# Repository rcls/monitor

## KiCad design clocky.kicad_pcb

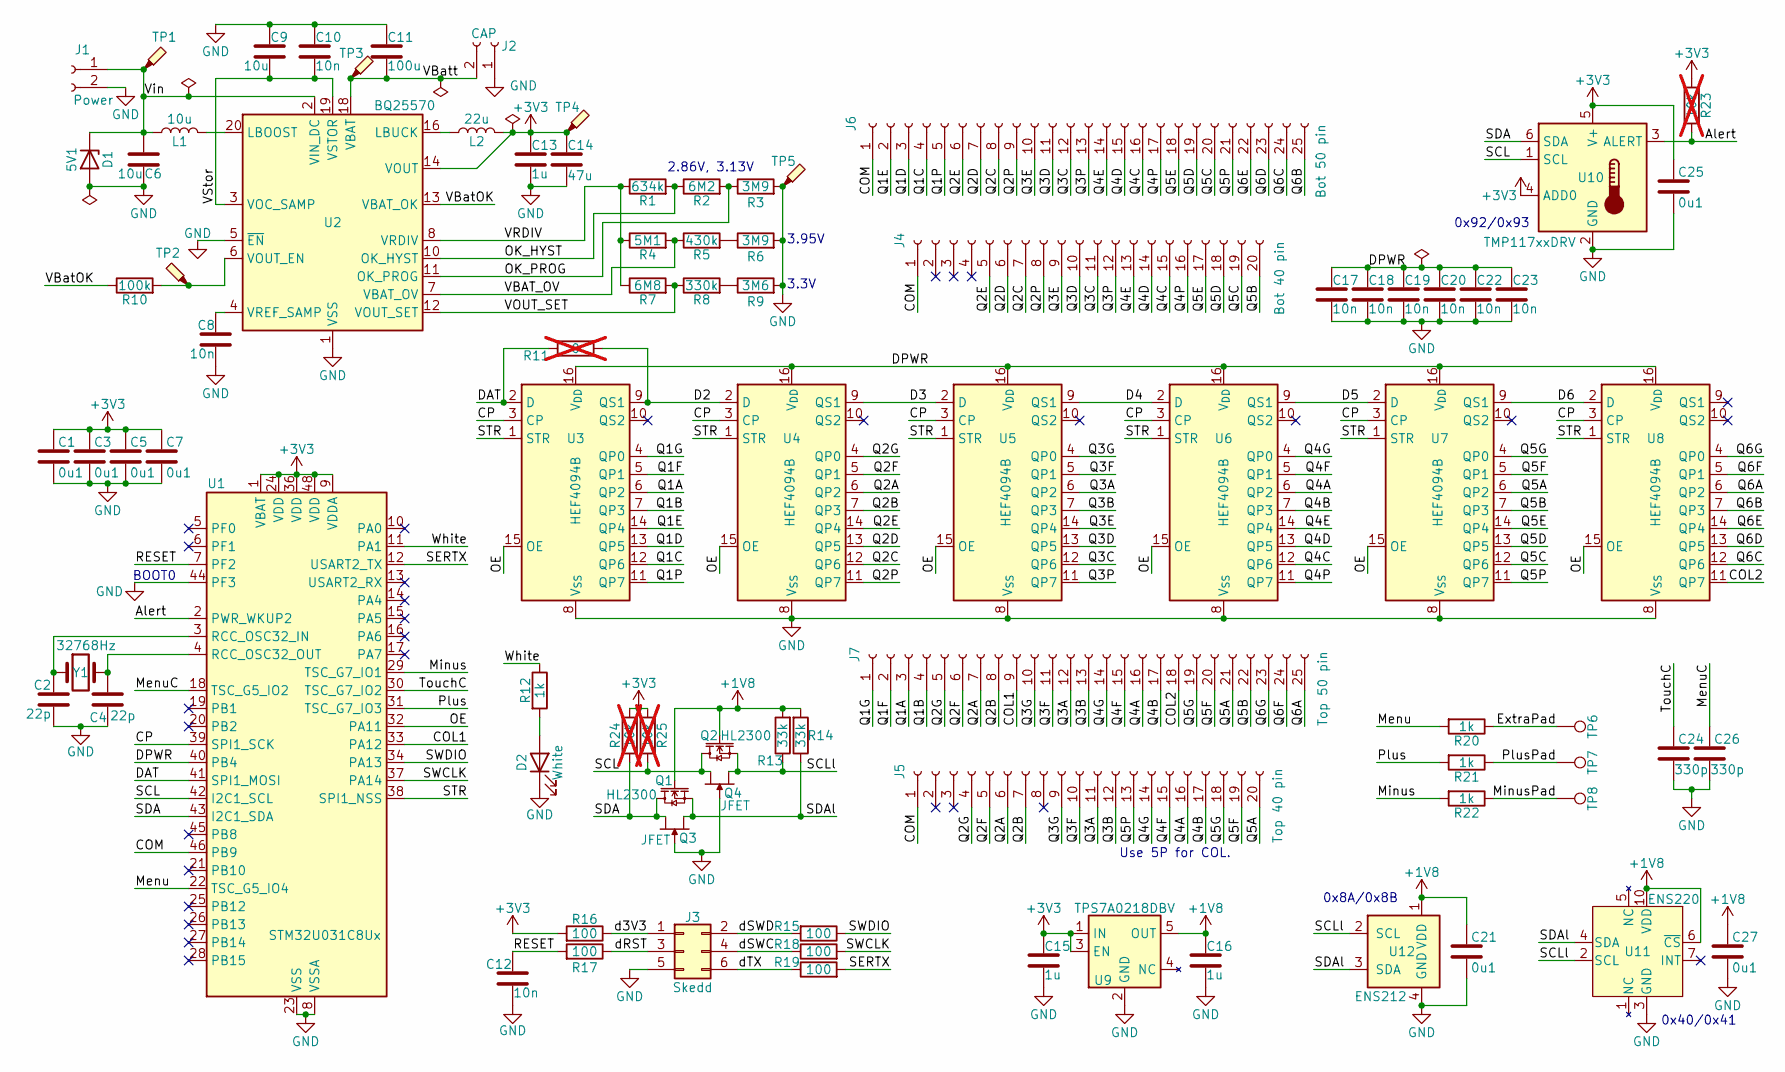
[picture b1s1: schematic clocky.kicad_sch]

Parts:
C1, C3, C5, C7, C21, C25, C27: 0u1; C_0402_1005Metric; JLCPCB C307331
C2, C4: 22p; C_0402_1005Metric; JLCPCB C1555
C6, C9: 10u; C_0603_1608Metric; JLCPCB C19702
C8, C10, C12, C17, C18, C19, C20, C22, C23: 10n; C_0402_1005Metric; JLCPCB C15195
C11: 100u; C_1206_3216Metric; JLCPCB C15008
C13, C15, C16: 1u; C_0402_1005Metric; JLCPCB C52923
C14: 47u; C_0805_2012Metric; JLCPCB C16780
C24, C26: 330p; C_0402_1005Metric; JLCPCB C13533
D1: 5V1; D_SOD-323; JLCPCB C19077434
D2: White; LED_0603_1608Metric; JLCPCB C2290
J1: Power; PinSocket_1x02_P2.54mm_Vertical
J2: CAP; TwoPin_P3.5mm
J3: Skedd; Skedd6
J4: Bot 40 pin; PinSocket_1x20_P2.54mm_Vertical
J5: Top 40 pin; PinSocket_1x20_P2.54mm_Vertical
J6: Bot 50 pin; PinHeader_1x25_P2.54mm_Vertical
J7: Top 50 pin; PinHeader_1x25_P2.54mm_Vertical
L1: 10u; L_0805_2012Metric_Pad1.05x1.20mm_HandSolder
L2: 22u; L_0805_2012Metric_Pad1.05x1.20mm_HandSolder
Q1, Q2: HL2300; SOT-23; JLCPCB C7420343
Q3, Q4: JFET; SOT-23-3
R1: 634k; R_0603_1608Metric
R2: 6M2; R_0603_1608Metric
R3, R6: 3M9; R_0603_1608Metric
R4: 5M1; R_0603_1608Metric
R5: 430k; R_0603_1608Metric; JLCPCB C25969
R7: 6M8; R_0603_1608Metric
R8: 330k; R_0603_1608Metric; JLCPCB C23137
R9: 3M6; R_0603_1608Metric
R10: 100k; R_0402_1005Metric; JLCPCB C25741
R11: 0; R_0603_1608Metric; not fitted
R12, R20, R21, R22: 1k; R_0402_1005Metric; JLCPCB C11702
R13, R14: 33k; R_0603_1608Metric; JLCPCB C4216
R15, R16, R17, R18, R19: 100; R_0402_1005Metric; JLCPCB C25076
R23, R24, R25: 10k; R_0603_1608Metric; not fitted
TP1, TP2, TP3, TP4, TP5: TestPoint_Probe; TestPoint
TP6, TP7, TP8: TestPoint; Dummy
U1: STM32U031C8Ux; QFN-48-1EP_7x7mm_P0.5mm_EP5.6x5.6mm
U2: BQ25570; QFN-20-1EP_3.5x3.5mm_P0.5mm_EP2x2mm; JLCPCB C506250
U3, U4, U5, U6, U7, U8: HEF4094B; SOIC-16_3.9x9.9mm_P1.27mm
U9: TPS7A0218DBV; SOT-23-5; JLCPCB C3748843
U10: TMP117xxDRV; WSON-6-1EP_2x2mm_P0.65mm_NoEP; JLCPCB C699536
U11: ENS220
U12: ENS212; AMS_QFN-4-1EP_2x2mm_P0.95mm_EP0.7x1.6mm
Y1: 32768Hz; Crystal_SMD_3215-2Pin_3.2x1.5mm; JLCPCB C32346

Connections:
+1V8: C16.1, C21.1, C27.1, Q1.1 (G), Q2.1 (G), R13.2, R14.2, U9.5 (OUT), U11.6 (~CS), U11.10 (VDD), U12.1 (VDD)
+3V3: C1.1, C3.1, C5.1, C7.1, C13.1, C14.1, C15.1, C25.1, L2.2, R16.2, R23.2, R24.2, R25.2, TP4.1, U1.1 (VBAT), U1.9 (VDDA), U1.24 (VDD), U1.36 (VDD), U1.48 (VDD), U2.14 (VOUT), U9.1 (IN), U9.3 (EN), U10.4 (ADD0), U10.5 (V+)
/Alert: R23.1, U1.2 (PWR_WKUP2), U10.3 (ALERT)
/COL1: J7.9, U1.33 (PA12)
/COL2: J7.18, U8.11 (QP7)
/COM: J4.1, J5.1, J6.1, U1.46 (PB9)
/CP: U1.39 (SPI1_SCK), U3.3 (CP), U4.3 (CP), U5.3 (CP), U6.3 (CP), U7.3 (CP), U8.3 (CP)
/D2: R11.2, U3.9 (QS1), U4.2 (D)
/D3: U4.9 (QS1), U5.2 (D)
/D4: U5.9 (QS1), U6.2 (D)
/D5: U6.9 (QS1), U7.2 (D)
/D6: U7.9 (QS1), U8.2 (D)
/DAT: R11.1, U1.41 (SPI1_MOSI), U3.2 (D)
/DPWR: C17.1, C18.1, C19.1, C20.1, C22.1, C23.1, U1.40 (PB4), U3.16 (V_{DD}), U4.16 (V_{DD}), U5.16 (V_{DD}), U6.16 (V_{DD}), U7.16 (V_{DD}), U8.16 (V_{DD})
/ExtraPad: R20.1, TP6.1
/Menu: R20.2, U1.22 (TSC_G5_IO4)
/MenuC: C26.1, U1.18 (TSC_G5_IO2)
/Minus: R22.2, U1.29 (TSC_G7_IO1)
/MinusPad: R22.1, TP8.1
/OE: U1.32 (PA11), U3.15 (OE), U4.15 (OE), U5.15 (OE), U6.15 (OE), U7.15 (OE), U8.15 (OE)
/OK_HYST: R1.2, R2.1, U2.10 (OK_HYST)
/OK_PROG: R2.2, R3.1, U2.11 (OK_PROG)
/Plus: R21.2, U1.31 (TSC_G7_IO3)
/PlusPad: R21.1, TP7.1
/Q1A: J7.3, U3.6 (QP2)
/Q1B: J7.4, U3.7 (QP3)
/Q1C: J6.4, U3.12 (QP6)
/Q1D: J6.3, U3.13 (QP5)
/Q1E: J6.2, U3.14 (QP4)
/Q1F: J7.2, U3.5 (QP1)
/Q1G: J7.1, U3.4 (QP0)
/Q1P: J6.5, U3.11 (QP7)
/Q2A: J5.6, J7.7, U4.6 (QP2)
/Q2B: J5.7, J7.8, U4.7 (QP3)
/Q2C: J4.7, J6.8, U4.12 (QP6)
/Q2D: J4.6, J6.7, U4.13 (QP5)
/Q2E: J4.5, J6.6, U4.14 (QP4)
/Q2F: J5.5, J7.6, U4.5 (QP1)
/Q2G: J5.4, J7.5, U4.4 (QP0)
/Q2P: J4.8, J6.9, U4.11 (QP7)
/Q3A: J5.11, J7.12, U5.6 (QP2)
/Q3B: J5.12, J7.13, U5.7 (QP3)
/Q3C: J4.11, J6.12, U5.12 (QP6)
/Q3D: J4.10, J6.11, U5.13 (QP5)
/Q3E: J4.9, J6.10, U5.14 (QP4)
/Q3F: J5.10, J7.11, U5.5 (QP1)
/Q3G: J5.9, J7.10, U5.4 (QP0)
/Q3P: J4.12, J6.13, U5.11 (QP7)
/Q4A: J5.16, J7.16, U6.6 (QP2)
/Q4B: J5.17, J7.17, U6.7 (QP3)
/Q4C: J4.15, J6.16, U6.12 (QP6)
/Q4D: J4.14, J6.15, U6.13 (QP5)
/Q4E: J4.13, J6.14, U6.14 (QP4)
/Q4F: J5.15, J7.15, U6.5 (QP1)
/Q4G: J5.14, J7.14, U6.4 (QP0)
/Q4P: J4.16, J6.17, U6.11 (QP7)
/Q5A: J5.20, J7.21, U7.6 (QP2)
/Q5B: J4.20, J7.22, U7.7 (QP3)
/Q5C: J4.19, J6.20, U7.12 (QP6)
/Q5D: J4.18, J6.19, U7.13 (QP5)
/Q5E: J4.17, J6.18, U7.14 (QP4)
/Q5F: J5.19, J7.20, U7.5 (QP1)
/Q5G: J5.18, J7.19, U7.4 (QP0)
/Q5P: J5.13, J6.21, U7.11 (QP7)
/Q6A: J7.25, U8.6 (QP2)
/Q6B: J6.25, U8.7 (QP3)
/Q6C: J6.24, U8.12 (QP6)
/Q6D: J6.23, U8.13 (QP5)
/Q6E: J6.22, U8.14 (QP4)
/Q6F: J7.24, U8.5 (QP1)
/Q6G: J7.23, U8.4 (QP0)
/RESET: C12.1, R17.2, U1.7 (PF2)
/SCL: Q2.3 (D), Q4.2 (S), R25.1, U1.42 (I2C1_SCL), U10.1 (SCL)
/SCLl: Q2.2 (S), Q4.1 (D), R13.1, U11.2 (SCL), U12.2 (SCL)
/SDA: Q1.3 (D), Q3.1 (D), R24.1, U1.43 (I2C1_SDA), U10.6 (SDA)
/SDAl: Q1.2 (S), Q3.2 (S), R14.1, U11.4 (SDA), U12.3 (SDA)
/SERTX: R19.2, U1.12 (USART2_TX)
/STR: U1.38 (SPI1_NSS), U3.1 (STR), U4.1 (STR), U5.1 (STR), U6.1 (STR), U7.1 (STR), U8.1 (STR)
/SWCLK: R18.2, U1.37 (PA14)
/SWDIO: R15.1, U1.34 (PA13)
/TouchC: C24.1, U1.30 (TSC_G7_IO2)
/VBAT_OV: R4.2, R5.1, U2.7 (VBAT_OV)
/VBatOK: R10.1, U2.13 (VBAT_OK)
/VBatt: C11.2, J2.2, TP3.1, U2.18 (VBAT)
/VOUT_SET: R7.2, R8.1, U2.12 (VOUT_SET)
/VRDIV: R1.1, R4.1, R7.1, U2.8 (VRDIV)
/VStor: C9.2, C10.2, U2.3 (VOC_SAMP), U2.19 (VSTOR)
/Vin: C6.1, D1.1 (K), J1.1, L1.1, TP1.1, U2.2 (VIN_DC)
/White: R12.1, U1.11 (PA1)
/d3V3: J3.1, R16.1
/dRST: J3.3, R17.1
/dSWC: J3.4, R18.1
/dSWD: J3.2, R15.2
/dTX: J3.6, R19.1
GND: C1.2, C2.2, C3.2, C4.2, C5.2, C6.2, C7.2, C8.2, C9.1, C10.1, C11.1, C12.2, C13.2, C14.2, C15.2, C16.2, C17.2, C18.2, C19.2, C20.2, C21.2, C22.2, C23.2, C24.2, C25.2, C26.2, C27.2, D1.2 (A), D2.1 (K), J1.2, J2.1, J3.5, Q3.3 (G), Q4.3 (G), R3.2, R6.2, R9.2, TP5.1, U1.8 (VSSA), U1.23 (VSS), U1.35 (VSS), U1.44 (PF3), U1.47 (VSS), U1.49 (VSS), U2.1 (VSS), U2.5 (~EN), U2.9 (VSS), U2.15 (VSS), U2.17 (VSS), U2.21 (VSS), U3.8 (V_{SS}), U4.8 (V_{SS}), U5.8 (V_{SS}), U6.8 (V_{SS}), U7.8 (V_{SS}), U8.8 (V_{SS}), U9.2 (GND), U10.2 (GND), U11.3 (GND), U11.8 (GND), U11.9 (GND), U12.4 (GND), U12.5 (GND)
unnamed: D2.2 (A), R12.2
unnamed: R5.2, R6.1
unnamed: R8.2, R9.1
unnamed: C2.1, U1.3 (RCC_OSC32_IN), Y1.1
unnamed: C4.1, U1.4 (RCC_OSC32_OUT), Y1.2
unnamed: L1.2, U2.20 (LBOOST)
unnamed: L2.1, U2.16 (LBUCK)
unnamed: R10.2, TP2.1, U2.6 (VOUT_EN)
unnamed: C8.1, U2.4 (VREF_SAMP)

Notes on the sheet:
3.95V
3.3V
0x8A/0x8B
BOOT0
2.86V, 3.13V
0x40/0x41
Use 5P for COL.
0x92/0x93

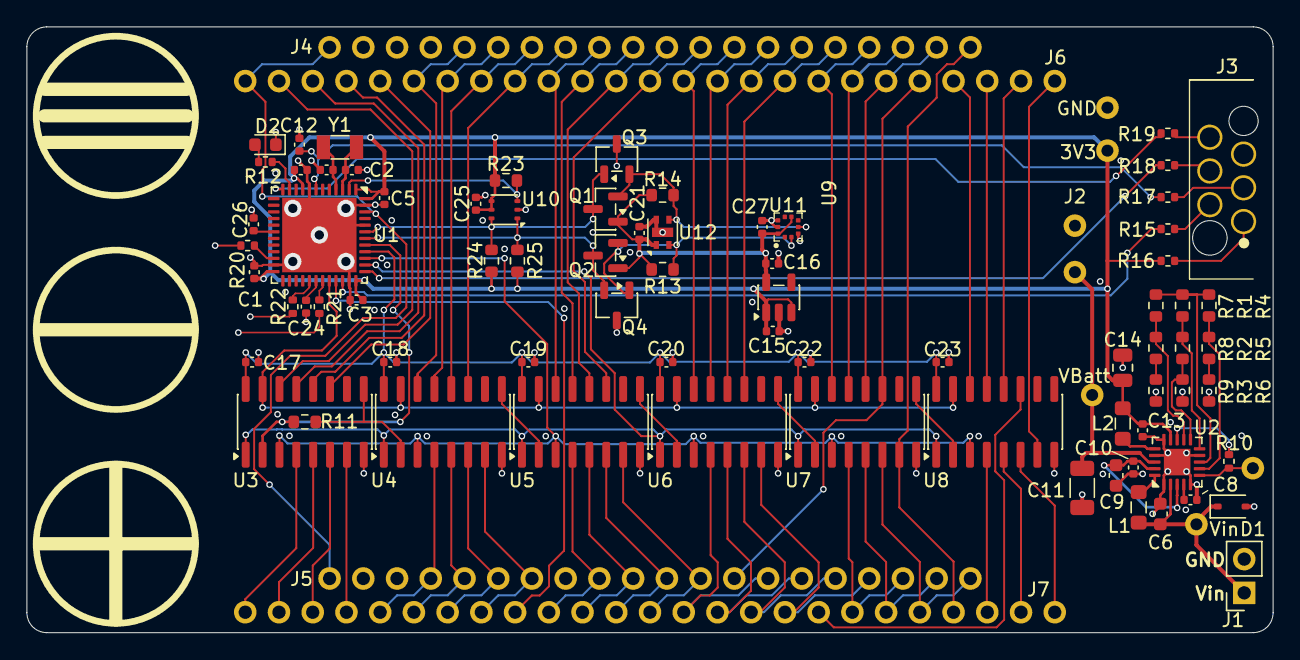
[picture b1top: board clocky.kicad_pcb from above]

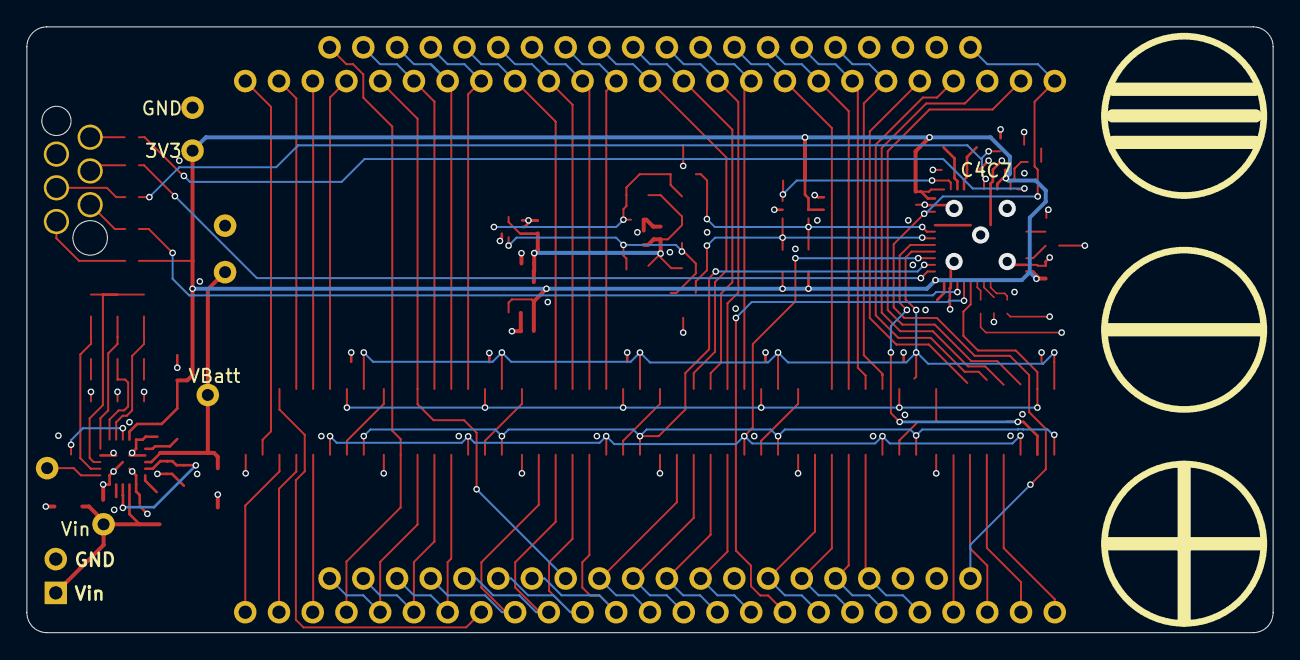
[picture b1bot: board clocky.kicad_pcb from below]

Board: 4 copper layers, 93.9 x 45.6 mm, 88 parts (5 on the bottom side), 104 nets.

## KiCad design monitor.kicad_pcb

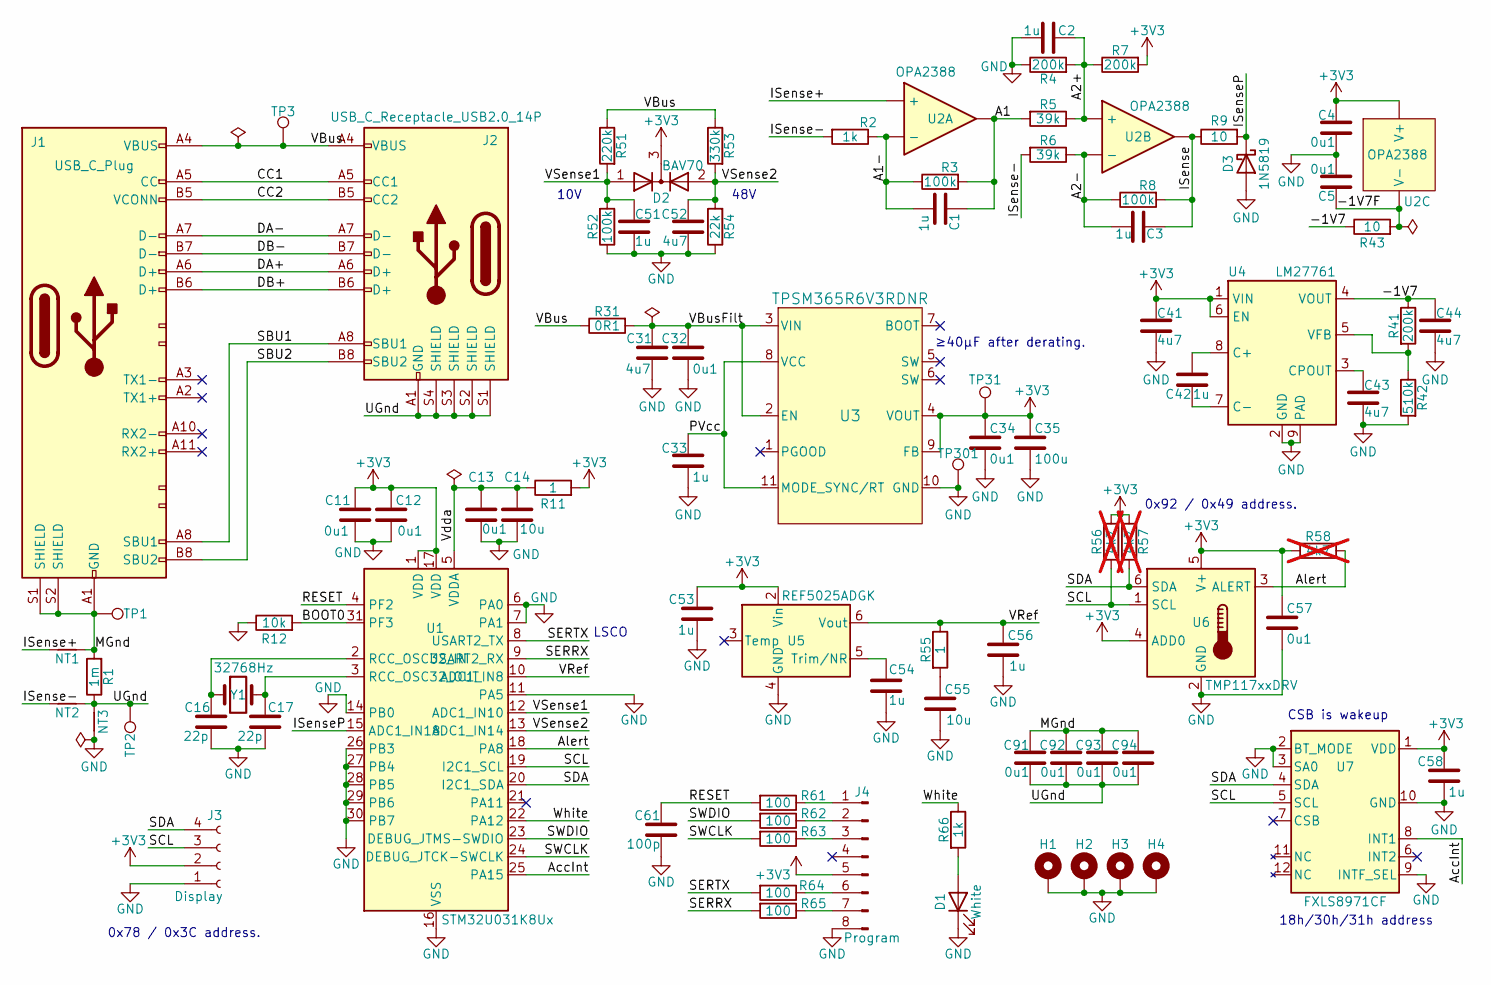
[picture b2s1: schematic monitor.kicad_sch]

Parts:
C1, C2, C3, C33, C42, C51, C53, C54, C56, C58: 1u; C_0402_1005Metric; JLCPCB C52923
C4, C5, C11, C12, C13, C32, C34, C57: 0u1; C_0402_1005Metric; JLCPCB C307331
C14, C55: 10u; C_0402_1005Metric; JLCPCB C15525
C16, C17: 22p; C_0402_1005Metric; JLCPCB C1555
C31: 4u7; C_1206_3216Metric; JLCPCB C29823
C35: 100u; C_1206_3216Metric; JLCPCB C15008
C41, C43, C44, C52: 4u7; C_0402_1005Metric; JLCPCB C23733
C61: 100p; C_0402_1005Metric; JLCPCB C1546
C91, C92, C93, C94: 0u1; C_0402_1005Metric
D1: White; LED_0603_1608Metric; JLCPCB C2290
D2: BAV70; SOT-23; JLCPCB C68978
D3: 1N5819; D_SOD-323; JLCPCB C191023
H1, H2, H3, H4: MountingHole_Pad; MountingHole_3mm_Pad
J1: USB_C_Plug; USB-C-male-24-Ass
J2: USB_C_Receptacle_USB2.0_14P; USB_C_Receptacle_16P
J3: Display; JST_XH_B4B-XH-A_1x04_P2.50mm_Vertical
J4: Program; PinHeader_1x08_P2.54mm_Vertical
NT1, NT2: NetTie_2; NetTie-2_0.2mm
NT3: NetTie_2; NetTie-2_SMD_Pad0.5mm
R1: 1m; R_1206_3216Metric
R2: 1k; R_0603_1608Metric; JLCPCB C21190
R3, R8, R52: 100k; R_0603_1608Metric; JLCPCB C25803
R4, R7: 200k; R_0603_1608Metric; JLCPCB C25811
R5, R6: 39k; R_0603_1608Metric; JLCPCB C23153
R9, R43: 10; R_0402_1005Metric; JLCPCB C25077
R11, R55: 1; R_0402_1005Metric; JLCPCB C25086
R12: 10k; R_0402_1005Metric; JLCPCB C25744
R31: 0R1; R_0603_1608Metric
R41: 200k; R_0402_1005Metric; JLCPCB C25764
R42: 510k; R_0402_1005Metric; JLCPCB C11616
R51: 220k; R_0603_1608Metric; JLCPCB C22961
R53: 330k; R_0603_1608Metric; JLCPCB C23137
R54: 22k; R_0603_1608Metric; JLCPCB C31850
R56, R57, R58: 4k7; R_0603_1608Metric; not fitted
R61, R62, R63, R64, R65: 100; R_0402_1005Metric; JLCPCB C25076
R66: 1k; R_0402_1005Metric; JLCPCB C11702
TP1, TP2, TP3, TP31, TP301: TestPoint
U1: STM32U031K8Ux; QFN-32-1EP_5x5mm_P0.5mm_EP3.45x3.45mm; JLCPCB C22445362
U2: OPA2388; MSOP-8_3x3mm_P0.65mm; JLCPCB C2059281
U3: TPSM365R6V3RDNR; RDN0011A-MFG; JLCPCB C18208843
U4: LM27761; WSON-8-1EP_2x2mm_P0.5mm_EP0.9x1.6mm; JLCPCB C129351
U5: REF5025ADGK; MSOP-8_3x3mm_P0.65mm; JLCPCB C75881
U6: TMP117xxDRV; WSON-6-1EP_2x2mm_P0.65mm_NoEP; JLCPCB C699536
U7: FXLS8971CF; JLCPCB C24123558
Y1: 32768Hz; Crystal_SMD_3215-2Pin_3.2x1.5mm; JLCPCB C32346

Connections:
+3V3: C4.1, C11.1, C12.1, C34.1, C35.1, C41.1, C53.1, C57.1, C58.1, D2.3 (K), J3.2, J4.5, R7.2, R11.2, R56.1, R57.1, R58.1, TP31.1, U1.1 (VDD), U1.17 (VDD), U2.8 (V+), U3.4 (VOUT), U3.9 (FB), U4.1 (VIN), U4.6 (EN), U5.2 (Vin), U6.4 (ADD0), U6.5 (V+), U7.1 (VDD)
/-1V7: C44.1, R41.1, R43.1, U4.4 (VOUT)
/-1V7F: C5.2, R43.2, U2.4 (V-)
/A1: C1.1, R3.2, R5.2, U2.1
/A1-: C1.2, R2.1, R3.1, U2.2 (-)
/A2+: C2.1, R4.2, R5.1, R7.1, U2.5 (+)
/A2-: C3.2, R6.1, R8.1, U2.6 (-)
/AccInt: U1.25 (PA15), U7.8 (INT1)
/Alert: R58.2, U1.18 (PA8), U6.3 (ALERT)
/BOOT0: R12.2, U1.31 (PF3)
/CC1: J1.A5 (CC), J2.A5 (CC1)
/CC2: J1.B5 (VCONN), J2.B5 (CC2)
/DA+: J1.A6 (D+), J2.A6 (D+)
/DA-: J1.A7 (D-), J2.A7 (D-)
/DB+: J1.B6 (D+), J2.B6 (D+)
/DB-: J1.B7 (D-), J2.B7 (D-)
/ISense: C3.1, R8.2, R9.1, U2.7
/ISense+: NT1.2, U2.3 (+)
/ISense-: NT2.2, R2.2, R6.2
/ISenseP: D3.1 (K), R9.2, U1.15 (ADC1_IN18)
/MGnd: C91.1, C92.1, C93.1, C94.1, J1.A1 (GND), J1.A12 (GND), J1.B1 (GND), J1.B12 (GND), J1.S1 (SHIELD), J1.S2 (SHIELD), NT1.1, R1.2, TP1.1
/PVcc: C33.1, U3.8 (VCC), U3.11 (MODE_SYNC/RT)
/RESET: C61.1, R61.2, U1.4 (PF2)
/SBU1: J1.A8 (SBU1), J2.A8 (SBU1)
/SBU2: J1.B8 (SBU2), J2.B8 (SBU2)
/SCL: J3.3, R56.2, U1.19 (I2C1_SCL), U6.1 (SCL), U7.5 (SCL)
/SDA: J3.4, R57.2, U1.20 (I2C1_SDA), U6.6 (SDA), U7.4 (SDA)
/SERRX: R65.2, U1.9 (USART2_RX)
/SERTX: R64.2, U1.8 (USART2_TX)
/SWCLK: R63.2, U1.24 (DEBUG_JTCK-SWCLK)
/SWDIO: R62.2, U1.23 (DEBUG_JTMS-SWDIO)
/UGnd: C91.2, C92.2, C93.2, C94.2, J2.A1 (GND), J2.A12 (GND), J2.B1 (GND), J2.B12 (GND), J2.S1 (SHIELD), J2.S2 (SHIELD), J2.S3 (SHIELD), J2.S4 (SHIELD), NT2.1, NT3.2, R1.1, TP2.1
/VBus: J1.A4 (VBUS), J1.A9 (VBUS), J1.B4 (VBUS), J1.B9 (VBUS), J2.A4 (VBUS), J2.A9 (VBUS), J2.B4 (VBUS), J2.B9 (VBUS), R31.1, R51.1, R53.1, TP3.1
/VBusFilt: C31.1, C32.1, R31.2, U3.2 (EN), U3.3 (VIN)
/VRef: C56.1, R55.1, U1.10 (ADC1_IN8), U5.6 (Vout)
/VSense1: C51.1, D2.1 (A), R51.2, R52.2, U1.12 (ADC1_IN10)
/VSense2: C52.1, D2.2 (A), R53.2, R54.2, U1.13 (ADC1_IN14)
/Vdda: C13.1, C14.1, R11.1, U1.5 (VDDA)
/White: R66.1, U1.22 (PA12)
GND: C2.2, C4.2, C5.1, C11.2, C12.2, C13.2, C14.2, C16.2, C17.2, C31.2, C32.2, C33.2, C34.2, C35.2, C41.2, C43.2, C44.2, C51.2, C52.2, C53.2, C54.2, C55.2, C56.2, C57.2, C58.2, C61.2, D1.1 (K), D3.2 (A), H1.1, H2.1, H3.1, H4.1, J3.1, J4.8, NT3.1, R4.1, R12.1, R42.2, R52.1, R54.1, TP301.1, U1.6 (PA0), U1.7 (PA1), U1.11 (PA5), U1.14 (PB0), U1.16 (VSS), U1.26 (PB3), U1.27 (PB4), U1.28 (PB5), U1.29 (PB6), U1.30 (PB7), U1.32 (VSS), U1.33 (VSS), U3.10 (GND), U4.2 (GND), U4.9 (PAD), U5.4 (GND), U6.2 (GND), U7.2 (BT_MODE), U7.3 (SA0), U7.9 (INTF_SEL), U7.10 (GND)
unnamed: C55.1, R55.2
unnamed: D1.2 (A), R66.2
unnamed: J4.1, R61.1
unnamed: J4.2, R62.1
unnamed: J4.3, R63.1
unnamed: J4.6, R64.1
unnamed: J4.7, R65.1
unnamed: C16.1, U1.2 (RCC_OSC32_IN), Y1.1
unnamed: C17.1, U1.3 (RCC_OSC32_OUT), Y1.2
unnamed: C42.1, U4.8 (C+)
unnamed: C42.2, U4.7 (C-)
unnamed: C43.1, U4.3 (CPOUT)
unnamed: R41.2, R42.1, U4.5 (VFB)
unnamed: C54.1, U5.5 (Trim/NR)

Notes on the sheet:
0x92 / 0x49 address.
18h/30h/31h address
LSCO
≥40µF after derating.
48V
CSB is wakeup
10V
0x78 / 0x3C address.

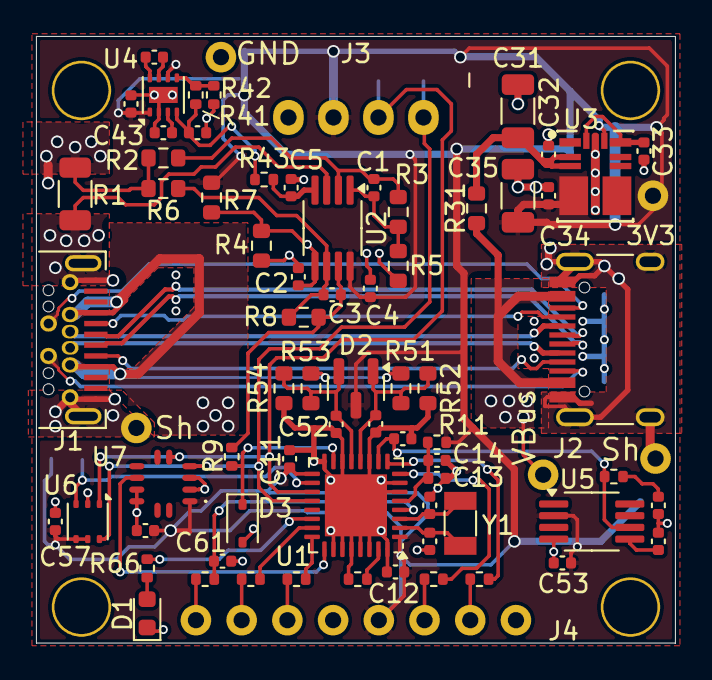
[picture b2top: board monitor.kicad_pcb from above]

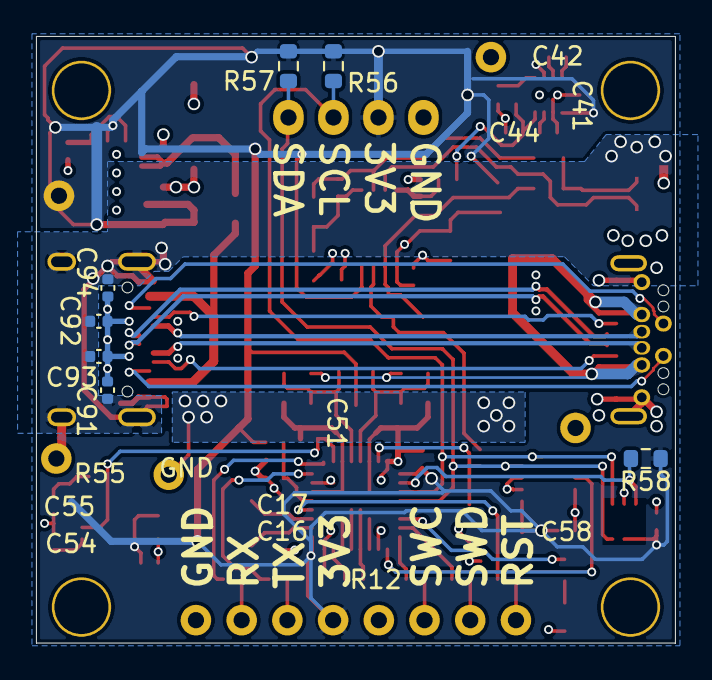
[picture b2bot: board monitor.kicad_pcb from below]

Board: 4 copper layers, 35.5 x 33.7 mm, 89 parts (11 on the bottom side), 54 nets.

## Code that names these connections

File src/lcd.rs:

#![allow(non_upper_case_globals)]

use stm_common::utils::WFE;

pub const WIDTH: usize = crate::LCD_WIDTH as usize;
pub const BITS: usize = WIDTH as usize * 8;

pub const SEG_A: u8 = 32;
pub const SEG_B: u8 = 16;
pub const SEG_C: u8 = 2;
pub const SEG_D: u8 = 4;
pub const SEG_E: u8 = 8;
pub const SEG_F: u8 = 64;
pub const SEG_G: u8 = 128;
pub const DOT: u8 = 1;

pub const D0: u8 = D8 & !MINUS;
pub const D1: u8 = SEG_B | SEG_C;
pub const D2: u8 = D8 & !SEG_C & !SEG_F;
pub const D3: u8 = D9 & !SEG_F;
pub const D4: u8 = D1 | SEG_F | SEG_G;
pub const D5: u8 = D9 & !SEG_B;
pub const D6: u8 = D5 | SEG_E;
pub const D7: u8 = D1 | SEG_A;
pub const D8: u8 = !DOT;
pub const D9: u8 = D8 & !SEG_E;

pub const DEG: u8 = SEG_A | SEG_B | SEG_F | SEG_G;
pub const DA: u8 = D8 & !SEG_D;
pub const Db: u8 = D6 & !SEG_A;
pub const DC: u8 = D0 & !SEG_B & !SEG_C;
pub const Dc: u8 = Do & !SEG_C;
pub const Dd: u8 = D8 & !SEG_A & !SEG_F;
pub const DE: u8 = D6 & !SEG_C;
pub const DF: u8 = DE & !SEG_D;
pub const DG: u8 = DC | SEG_C;
pub const Dh: u8 = Dn | SEG_F;
pub const Di: u8 = SEG_C;
pub const Dn: u8 = Do & !SEG_D;
pub const Do: u8 = Dd & !SEG_B;
pub const DP: u8 = DEG | SEG_E;
pub const Dt: u8 = Db & !SEG_C;
pub const Du: u8 = Do & !SEG_G;

pub const MINUS: u8 = SEG_G;
/// Right or only colon.
pub const COL2: Segments = 1;
/// Left colon on wide display.
pub const COL1: Segments = if WIDTH == 6 {1 << 48} else {0};

pub trait SegmentsTrait<const N: usize> {type Segments;}
impl SegmentsTrait<6> for () {type Segments = u64;}
impl SegmentsTrait<4> for () {type Segments = u32;}
pub type Segments = <() as SegmentsTrait<{WIDTH}>>::Segments;
pub type SegArray = [u8; size_of::<Segments>()];

pub static DIGITS: [u8; 16] = [
    D0, D1, D2, D3, D4, D5, D6, D7, D8, D9, DA, Db, DC, Dd, DE, DF];

/// Initialize the I/O to the LCD.
pub fn init() {
    let gpioa = unsafe {&*stm32u031::GPIOA::ptr()};
    let gpiob = unsafe {&*stm32u031::GPIOB::ptr()};
    let spi   = unsafe {&*stm32u031::SPI1 ::ptr()};

    const {assert!(crate::CONFIG.apb2_clocks & 1 << 12 != 0)};

    // Remove any standby pull-up/pull-downs.
    crate::cpu::Config::new(0).lcd().clear_pupd();

    // OE pin A11, CP=B3, DAT=B5, STR=A15, COM = B9.
    // Set OE to output low.
    // Set PWR=PB4 to be high.
    // Leave COM and COL1 (A12) as hi-z until we set the output.
    // gpioa.BSRR.write(|w| w.BR11().set_bit());
    gpioa.MODER.modify(|_,w| w.MODE11().B_0x1().MODE15().B_0x1());
    gpiob.BSRR.write(|w| w.BS4().set_bit());
    gpiob.MODER.modify(|_,w| w.MODE3().B_0x1().MODE4().B_0x1().MODE5().B_0x1());

    // Set the function (AF5) for the SPI pins CP (B3), DAT(B5).
    gpiob.AFRL.modify(|_,w| w.AFSEL3().B_0x5().AFSEL5().B_0x5());
    gpiob.MODER.modify(|_,w| w.MODE3().B_0x2().MODE5().B_0x2());

    // Set-up SPI1.
    spi.CR2.write(|w| w.DS().B_0xF().SSOE().set_bit());
    let br = (crate::CONFIG.clk / 1000000).ilog2() as u8;
    spi.CR1.write(
        |w| w.LSBFIRST().set_bit().SPE().set_bit().BR().bits(br)
            .MSTR().set_bit());
}

pub fn update_lcd(bits: Segments, comm: bool) {
    // Invert segment bits if comm is high.
    let bits = if comm {!bits} else {bits};

    let gpioa = unsafe {&*stm32u031::GPIOA::ptr()};
    let gpiob = unsafe {&*stm32u031::GPIOB::ptr()};
    let spi   = unsafe {&*stm32u031::SPI1 ::ptr()};

    // Set OE (A11) and STR (A15) low.
    gpioa.BSRR.write(|w| w.BR11().set_bit().BR15().set_bit());

    // Set COL1 (A12) to high impedance (input).
    gpioa.MODER.modify(|_, w| w.MODE12().B_0x0());
    // Set COM (PB9) to high impedance.
    gpiob.MODER.modify(|_, w| w.MODE9().B_0x0());

    // Do one dummy data read before transmitting.  This will (eventually!)
    // clear out fifo-not-clear problems.
    spi.DR.read();

    // We have a 32 bit fifo.
    spi.DR.write(|w| w.bits((bits & 0xffff) as u16));
    spi.DR.write(|w| w.bits((bits >> 16) as u16));
    // If we have have a third word to write, wait for one RX word then send it.
    if WIDTH == 6 {
        rx_word(spi);
        spi.DR.write(|w| w.bits((bits >> 16 >> 16) as u16));
    }
    // Wait for 2 words RX.
    rx_word(spi);
    rx_word(spi);

    // Set STR (A15) high.  Set col1 (A12), it's not driven yet.  (If both S and
    // R are set, then S wins.)
    let col1 = if WIDTH == 6 {bits as u64 & 1 << 48 != 0} else {comm};
    gpioa.BSRR.write(|w|
        w.BS15().set_bit().BS12().bit(col1).BR12().set_bit());

    // Set COM polarity.
    gpiob.BSRR.write(|w| w.BS9().bit(comm).BR9().set_bit());
    // Drive com.
    gpiob.MODER.modify(|_, w| w.MODE9().B_0x1());

    // Set OE & STR.
    gpioa.BSRR.write(|w| w.BS11().set_bit().BS15().set_bit());
    // Drive COL1.
    gpioa.MODER.modify(|_, w| w.MODE12().B_0x1());
}

#[inline(never)]
fn rx_word(spi: &stm32u031::spi1::RegisterBlock) {
    let nvic = unsafe {&*cortex_m::peripheral::NVIC::PTR};
    // SEVONPEND only wakes up on the rising edge of the pending flag.  So we
    // need to clear the flag.
    unsafe {
        nvic.icpr[0].write(1 << stm32u031::Interrupt::SPI1 as u32);
    }
    // Make sure we actually get a rising edge on the interrupt!
    let cr2 = spi.CR2.read().bits();
    spi.CR2.write(|w| w.bits(cr2).RXNEIE().set_bit());
    loop {
        WFE(); // We rely on SEVONPEND to wake us up.
        if spi.SR.read().RXNE().bit() {
            break;
        }
    }
    spi.CR2.write(|w| w.bits(cr2).RXNEIE().clear_bit());
    spi.DR.read();
}

/// Best effort if it doesn't fit - return trailing digits!
pub fn signed_to_segments(segs: &mut SegArray, v: i32, min: usize) -> usize {
    let u = crate::utils::to_bcd(v.unsigned_abs());
    format_hex(segs, u, min, v < 0)
}

#[inline(never)]
pub fn hex_to_segments(value: u32) -> SegArray {
    let mut segs = [0; _];
    format_hex(&mut segs, value, WIDTH, false);
    segs
}

pub fn format_hex(segs: &mut SegArray, u: u32, min: usize, neg: bool)
        -> usize {
    let mut i = segs.iter_mut();
    let mut count = 0;
    let mut u = u as usize;
    loop {
        let Some(p) = i.next() else {return count};
        *p = DIGITS[u % 16];
        u /= 16;
        count += 1;
        if count >= WIDTH {
            return count;
        }
        if u == 0 && count >= min {
            break;
        }
    }
    if neg && let Some(p) = i.next() {
        *p = MINUS;
        count += 1;
    }
    count
}

impl crate::cpu::Config {
    pub const fn lcd(&mut self) -> &mut Self {
        // Preserve the control lines.
        self.standby_pu |= 1 << 11 | 1 << 0x14; // OE, DPWR.
        self.standby_pd |= 1 << 15 | 1 << 0x13; // STR, CP
        self.keep_pu    |= 1 << 12 | 1 << 0x15 | 1 << 0x19; // COL, DAT, COM.
        self.keep_pd    |= 1 << 12 | 1 << 0x15 | 1 << 0x19; // COL, DAT, COM.
        self.clocks(0, 0, 1 << 12)
    }
}

#[cfg(test)]
pub fn segments_to_str(s: Segments) -> String {
    let mut result = Vec::<char>::new();
    for b in &s.to_le_bytes()[0..WIDTH] {
        let b = b & !DOT;
        let c = match b {
            DEG => '°',
            MINUS => '-',
            DC => 'C',
            0 => ' ',
            _ => char::from_u32(
                48 + DIGITS.iter().position(|x| *x == b).unwrap() as u32)
                .unwrap(),
        };
        result.push(c);
    }
    for (i, b) in s.to_le_bytes()[0..WIDTH].iter().enumerate().skip(1).rev() {
        let colon = match i {
            2 => s & COL2 != 0,
            4 => s & COL1 != 0,
            _ => false};
        let sep = if b & DOT != 0 {
            if colon {'⋮'} else {'.'}
        }
        else if colon {':'} else {continue};
        result.insert(i, sep);
    }
    result.iter().rev().collect()
}

#[test]
fn check_decimal() {
    fn expected(v: i32, min: usize) -> String {
        let min = min.max(1);
        let mut s = format!("{:0min$}", v.unsigned_abs());
        if v < 0 {
            s.insert(0, '-');
        }
        while s.len() < WIDTH {
            s.insert(0, ' ');
        }
        if s.len() > WIDTH {
            s.replace_range(.. s.len() - WIDTH, "");
        }
        s
    }
    for i in -65535 ..= 65535 {
        for min in 0 ..= 2 {
            let mut segs = SegArray::default();
            let p = signed_to_segments(&mut segs, i, min);
            assert!(p > 0);
            assert!(p == segs.len() || segs[p] == 0);
            assert!(segs[p - 1] != 0);
            let segs = Segments::from_le_bytes(segs);
            assert_eq!(segments_to_str(segs), expected(i, min));
        }
    }
}

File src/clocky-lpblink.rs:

#![cfg_attr(target_os = "none", no_std)]
#![cfg_attr(target_os = "none", no_main)]
#![allow(internal_features)]
#![allow(unpredictable_function_pointer_comparisons)]
#![feature(const_default)]
#![feature(const_trait_impl)]
#![feature(derive_const)]
#![feature(format_args_nl)]
#![feature(link_llvm_intrinsics)]

mod cpu;
mod debug;
mod dma;
mod i2c;
#[allow(dead_code)]
mod lcd;
mod low_power;
mod utils;
mod vcell;

type LcdBits = u64;
const LCD_BITS: u32
    = match size_of::<LcdBits>() {4 => 32, 8 => 48, _ => panic!()};

const I2C_LINES: i2c::I2CLines = i2c::I2CLines::B6_B7;

const CONFIG: cpu::Config = {
    let mut cfg = cpu::Config::new(2000000);
    cfg.pullup |= 1 << 0x2d;
    cfg.standby_pu |= 1 << 0x2d; // PC13.
    cfg.pupd_use_pwr = true;
    *cfg.lazy_debug().lazy_i2c().lcd()
};

const MAGIC: u32 = 0xc6ea33e;

fn cold_start() {
    let pwr = unsafe {&*stm32u031::PWR::ptr()};

    dbgln!("**** RESTART ****");
    let tamp = unsafe {&*stm32u031::TAMP::ptr()};
    tamp.BKPR[0].write(|w| w.bits(MAGIC));
    low_power::ensure_options();
    low_power::rtc_setup_20Hz();

    // Initialize the TMP117 by requesting a conversion.
    i2c::init();
    const CONFIG: u16 = 0x0c04; // One shot, alert when ready.
    let _ = i2c::write(i2c::TMP117, &[1u8, (CONFIG >> 8) as u8, CONFIG as u8])
        .wait();

    // Alert is hot-wired to PC13, WKUP2.  Set it to falling edge triggered.
    pwr.CR4.write(|w| w.WP2().set_bit());
    pwr.CR3.modify(|_,w| w.EIWUL().set_bit().EWUP2().set_bit());
    // Clear the wake-up pin as it has probably gotten set during start-up.
    pwr.SCR.write(|w| w.CWUF2().set_bit());
}

fn segments(temp: i32) -> u32 {
    let mut segs = lcd::DOT as u32 * 256;
    let mut p = 0;
    let mut quo = temp.unsigned_abs() as u16;
    while p < 32 && quo != 0 || p < 16 {
        let rem = quo % 10;
        quo = quo / 10;
        segs += (lcd::DIGITS[rem as usize] as u32) << p;
        p += 8;
    }
    if p < 32 && temp < 0 {
        segs += (lcd::MINUS as u32) << p;
    }
    segs
}

fn display(segments: u32, seq: u32) {
    let com = seq & 1 != 0;
    if LCD_BITS == 48 {
        let shift = seq as u16 % 48 & !7;
        let segments = segments as LcdBits;
        let segments = segments << shift | segments >> 48 - shift;
        lcd::update_lcd(segments, com);
    }
    else {
        lcd::update_lcd(segments as LcdBits, com);
    }
}

fn alert() {
    let pwr = unsafe {&*stm32u031::PWR::ptr()};
    let tamp = unsafe {&*stm32u031::TAMP::ptr()};

    // Disable the pullup on PC13 while we do the I2C.
    pwr.PUCRC.write(|w| w.bits(0));
    i2c::init();

    // Read the temperature...
    let mut countsbe = 0i16;
    let _ = i2c::read_reg(i2c::TMP117, 0, &mut countsbe).wait();
    // The docs say we need a read of config to clear the alert.
    let _ = i2c::read_reg(i2c::TMP117, 1, &mut 0i16).wait();
    let counts = i16::from_be(countsbe) as i32;
    let temp = counts_to_temp(counts);
    //dbgln!("Alert! {} {}", temp, tamp.BKPR[1].read().bits());
    // Write the alert high and low registers.
    let upper = next_temp(temp).max(counts + 3).min( 0x7fff);
    let lower = prev_temp(temp).min(counts - 3).max(-0x8000);
    let _ = i2c::write(i2c::TMP117, &[2u8, (upper >> 8) as u8, upper as u8]);
    let _ = i2c::write(i2c::TMP117, &[3u8, (lower >> 8) as u8, lower as u8]);

    // The alert pin should be released.  Reenable the pull-up.
    pwr.PUCRC.write(|w| w.bits(1 << 13));

    let segments = segments(temp);
    tamp.BKPR[2].write(|w| w.bits(segments));
    // Updating the display can wait for the next tick.  Disable the wake-up.
    pwr.CR3.modify(|_,w| w.EIWUL().set_bit().EWUP2().clear_bit());
}

fn tick() {
    let pwr  = unsafe {&*stm32u031::PWR ::ptr()};
    let tamp = unsafe {&*stm32u031::TAMP::ptr()};

    let seq = tamp.BKPR[1].read().bits().wrapping_add(1);
    tamp.BKPR[1].write(|w| w.bits(seq));

    // On /32, command a conversion.
    let w;
    if seq & 31 == 0 {
        // Single shot conversion.  Arm and clear the wake-up flag.
        pwr.CR3.modify(|_,w| w.EIWUL().set_bit().EWUP2().set_bit());
        pwr.SCR.write(|w| w.CWUF2().set_bit());

        i2c::init();
        w = i2c::write(i2c::TMP117, &[1u8, 0xc, 0]);
    }
    else {
        w = i2c::Wait::new();
    }
    let segments = tamp.BKPR[2].read().bits();
    lcd::init();
    display(segments, seq);
    let _ = w.wait();
}

fn main() -> ! {
    let pwr  = unsafe {&*stm32u031::PWR ::ptr()};
    let rcc  = unsafe {&*stm32u031::RCC ::ptr()};
    let tamp = unsafe {&*stm32u031::TAMP::ptr()};

    // TODO - lazy set up of all the clocks!
    // Enable IO clocks.
    rcc.IOPENR.write(|w| w.GPIOAEN().set_bit().GPIOBEN().set_bit());

    // LED is on PA1.
    // let gpioa = unsafe {&*stm32u031::GPIOA::ptr()};
    // gpioa.MODER.write(|w| w.MODE1().B_0x1());
    // gpioa.BSRR.write(|w| w.BS1().set_bit());

    // Enable PWR before CPU init for now, so we get pristine values of
    // registers.
    // FIXME - work out what is needed now!
    rcc.APBENR1.modify(|_, w| w.PWREN().set_bit().RTCAPBEN().set_bit());

    cpu::init1();

    cpu::init2();

    let rcc_csr = rcc.CSR.read().bits();

    low_power::rtc_enable();

    let sr1 = pwr.SR1.read();

    // If all of the reset reason, the magic number, and the woke-from-standby
    // flag agree, treat this as a normal restart.  Else do a cold-start.
    if rcc_csr & 0xfe000000 != 0 || tamp.BKPR[0].read().bits() != MAGIC
        || !sr1.SBF().bit() {
        cold_start();
    }

    if sr1.WUF2().bit() {
        alert();
        // Processing alert() should give the pin time to rise.
        pwr.SCR.write(|w| w.CWUF2().set_bit());
    }
    if sr1.WUFI().bit() {
        tick();
    }

    low_power::standby();
}

fn counts_to_temp(c: i32) -> i32 {
    (c * 5 + 32) >> 6
}

fn next_temp(t: i32) -> i32 {
    let nm = t * 64 + 32 + 4;
    let nm = if nm >= 0 {nm} else {nm - 4};
    nm / 5
}

fn prev_temp(t: i32) -> i32 {
    let pm = t * 64 - 32 - 1;
    let pm = if pm >= 0 {pm} else {pm - 4};
    pm / 5
}

#[test]
fn check_next_temp() {
    for t in -999 ..= 1499 {
        let n = next_temp(t);
        assert_eq!(counts_to_temp(n), t + 1);
        assert_eq!(counts_to_temp(n - 1), t);
    }
}

#[test]
fn check_prev_temp() {
    for t in -999 ..= 1499 {
        let p = prev_temp(t);
        assert_eq!(counts_to_temp(p), t - 1);
        assert_eq!(counts_to_temp(p + 1), t);
    }
}

#[test]
fn test_segments() {
    for i in 0 ..= 9999 {
        let text = format!("{i:02}");
        let mut segs = 0;
        let mut minus = lcd::MINUS as u32;
        for c in text.chars() {
            segs = segs * 256 + lcd::DIGITS[c as usize - 48] as u32;
            minus <<= 8;
        }
        segs += lcd::DOT as u32 * 256;
        assert_eq!(segments(i), segs, "{i} {:x} {segs:x}", segments(i));
        if 0 < i && i <= 999 {
            assert_eq!(segments(-i), segs + minus);
        }
    }
}

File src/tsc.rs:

use stm_common::{utils::WFE, vcell::{UCell, VCell}};

///! Pads are +, -, menu.  Note that the index is one less than the enumeration.

/// Rev 1 board had high caps, rev 2 board had low caps.  This value is used to
/// distinguish them.
pub const LO_HI_SEP: u32 = 100;

/// Touch threshold used for low cap boards.
pub const LO_THRESHOLD: u32 = 26;

/// Touch threshold used for hi cap boards.
pub const HI_THRESHOLD: u32 = 1536;

// Little board gives 28..31 and 19..22
// Big board gives 27..30 and 19..20, threhold 22 or 23 would be good.

macro_rules!dbgln {($($tt:tt)*) => {if false {stm_common::dbgln!($($tt)*)}};}

struct State {
    values: UCell<[u32; 3]>,
    complete: VCell<bool>,
}

#[unsafe(link_section = ".noinit")]
static STATE: State = State {
    values: UCell::new([0; 3]), complete: VCell::new(false)};

pub mod pad {
    pub const NONE : u32 = 0;
    pub const PLUS : u32 = 1;
    #[allow(unused)]
    pub const MINUS: u32 = 2;
    pub const MENU : u32 = 3;
}

pub fn init() {
    let gpioa = unsafe {&*stm32u031::GPIOA::ptr()};
    let gpiob = unsafe {&*stm32u031::GPIOB::ptr()};
    let rcc = unsafe {&*stm32u031::RCC::ptr()};
    let tsc = unsafe {&*stm32u031::TSC::ptr()};

    // FIXME - hardwired channels & values.
    if crate::CONFIG.is_lazy_tsc() {
        rcc.AHBENR.modify(|_,w| w.TSCEN().set_bit());
    }

    gpioa.AFRH.modify(
        |_,w| w.AFSEL8().B_0x9().AFSEL9().B_0x9().AFSEL10().B_0x9());
    gpiob.AFRL.modify(|_,w| w.AFSEL0().B_0x9());
    gpiob.AFRH.modify(|_,w| w.AFSEL11().B_0x9());

    // Set open drain mode for the sampling cap pins.
    gpioa.OTYPER.modify(|_,w| w.OT9().B_0x1());
    gpiob.OTYPER.modify(|_,w| w.OT0().B_0x1());

    // Enable AF.
    gpioa.MODER.modify(|_,w| w.MODE8().B_0x2().MODE9().B_0x2().MODE10().B_0x2());
    gpiob.MODER.modify(|_,w| w.MODE0().B_0x2().MODE11().B_0x2());

    // Prescale to 2Mhz.
    let prescaler = match crate::CONFIG.clk {
        2000000 => 0,
        16000000 => 3,
        _ => stm_common::utils::unreachable(),
    };

    // TODO - timings are guesses...
    // Standard pulse range "500ns to 2µs".
    // Use 3 clock = 1.5µs on high and low pulse.
    // Spread-sprectrum on but as low as possible.
    // Max counts is set to 2048, values much below that count as a touch.
    tsc.CR.write(
        |w|w.CTPH().bits(1).CTPL().bits(2)
            .SSD().bits(0). SSE().set_bit().SSPSC().set_bit()
            .PGPSC().bits(prescaler).MCV().B_0x3().TSCE().set_bit());
    // Turning off hysteresis for the cap-sense lines seems to improve
    // sensitivity.
    tsc.IOHCR.write(|w| w.G7_IO2().clear_bit(). G5_IO2().clear_bit());
    // Enable end-of-acquire interrupt.
    tsc.IER.write(|w| w.EOAIE().set_bit());
}

pub fn acquire() {
    // Try + and menu on the first pass (they are physically separate), and
    // then - on the second pass.
    // FIXME - how do we select channels?

    // Minus  = G7IO1
    // CS     = G7IO2
    // Plus   = G7IO3
    // Menu   = G5IO4
    // MenuCS = G5IO2
    STATE.complete.write(false);
    let tsc = unsafe {&*stm32u031::TSC::ptr()};
    // Get + and cap.
    tsc.IOCCR.write(|w| w.G7_IO3().set_bit().G5_IO4().set_bit());
    tsc.IOSCR.write(|w| w.G7_IO2().set_bit().G5_IO2().set_bit());
    tsc.IOGCSR.write(|w| w.G7E().set_bit().G5E().set_bit());
    tsc.CR.modify(|_,w| w.START().set_bit());
}

fn isr() {
    let tsc = unsafe {&*stm32u031::TSC::ptr()};
    let sr = tsc.ISR.read().bits();
    tsc.ICR.write(|w| w.bits(sr));

    let ccr = tsc.IOCCR.read();
    let values = unsafe {STATE.values.as_mut()};
    if ccr.G7_IO3().bit() { // +
        values[0] = tsc.IOG7CR.read().bits();
    }
    if ccr.G5_IO4().bit() { // Menu
        values[2] = tsc.IOG5CR.read().bits();
    }
    if ccr.G7_IO1().bit() { // -
        // We got -, the pass is done.
        values[1] = tsc.IOG7CR.read().bits();
        STATE.complete.write(true);
    }
    else {
        // We did not get -, get - and menu now.
        tsc.IOCCR.write(|w| w.G7_IO1().set_bit());
        tsc.IOSCR.write(|w| w.G7_IO2().set_bit());
        tsc.IOGCSR.write(|w| w.G7E().set_bit());
        tsc.CR.modify(|_,w| w.START().set_bit());
    }
}

/// Return touched pad, 1=+, 2=-, 3=menu, 0=None.
pub fn retrieve() -> (u32, u32) {
    while !STATE.complete.read() {
        WFE();
    }
    // Find the lowest line...
    let mut min_line = 0;
    let values = STATE.values.as_ref();
    let mut min_val = values[0];
    let mut max_val = min_val;
    for (i, &val) in values.iter().enumerate().skip(1) {
        if val > max_val {
            max_val = val;
        }
        else if val < min_val {
            min_val = val;
            min_line = i as u32;
        }
    }
    dbgln!("TSC min {min_val} max {max_val}");

    let threshold = if max_val > LO_HI_SEP {HI_THRESHOLD} else {LO_THRESHOLD};
    let line = if min_val < threshold {min_line + 1} else {0};
    let debug6 = values[0] & 0xff | values[1] << 8 & 0xff00
        | values[2] << 16 & 0xff0000;
    let debug4 = min_val & 0xff | max_val << 8 & 0xff00;
    (line, if super::LCD_WIDTH == 6 {debug6} else {debug4})
}

impl crate::cpu::Config {
    pub const fn lazy_tsc(&mut self) -> &mut Self {
        self.isr(stm32u031::Interrupt::TSC, isr)
    }
    #[allow(dead_code)]
    pub const fn tsc(&mut self) -> &mut Self {
        self.lazy_tsc().clocks(1 << 24, 0, 0)
    }
    pub fn is_lazy_tsc(&self) -> bool {
        self.ahb_clocks & 1 << 24 == 0
    }
}

#[test]
fn check_isr() {
    assert!(crate::cpu::VECTORS.isr[stm32u031::Interrupt::TSC as usize]
        == isr);
}

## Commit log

2025-05-23 Schematics
2025-05-24 Monitor board layout
2025-05-24 Footprint tweaks.
2025-05-24 Manufacturing updates
2025-05-24 Robustify reset
2025-05-27 Second board layout routed.
2025-05-27 DRC passes.
2025-05-27 Sort the touch pads out a bit.
    Zones still need work.
2025-05-27 Update monitor for actual display
2025-05-27 Do a round of DRC and tidy-up.
2025-05-28 Do a round of tidy-up on clocky.
2025-05-29 Rotate CPU on clocky. Tidy up every where.
2025-05-29 Tweak power & zones.
2025-05-29 Use a 2.54mm connector footprint.
2025-05-29 Filter ADC input.
    Tweak other capacitors.
2025-05-30 Final updates. Ordered.
2025-06-23 First cut of some code
2025-06-25 Factor loads of stuff out.
    Change debug to be async.
2025-06-25 Tidy ups and tests.
2025-06-27 Lots of refactoring
2025-06-29 Flies
2025-06-30 I2C error handling. Power.
2025-07-01 Character handling updates.
2025-07-01 Redo the arrows.
2025-07-03 Minor updates.
2025-07-03 Blinky for clocky
2025-07-04 TMP on clocky works
2025-07-06 Big update to the monitor.
    Accell, low side current sense.
2025-07-06 Switch to the 2-stage sense amp.
2025-07-06 Board layout updated.
2025-07-07 Tweaks. Fabbing.
2025-07-09 Remove redundant verbiage.
2025-07-09 Update the python scripts.
2025-07-09 Debug now uses LPUART. Parameterize some things.
2025-07-09 Refactor monitor top level a bit.
2025-07-09 Exclusions.
2025-07-09 Factor out a heap of interrupt table set-up.
2025-07-09 More factoring out of start-up.
2025-07-11 Low power blinky
2025-07-11 Use sev-on-pend for polling
2025-07-11 Don't spin draining the UART.
2025-07-11 Clean-up.
2025-07-12 Factor out the power & standby handling
2025-07-14 Reduce binary size.
2025-07-14 Only one debug, works for both sync and async.
2025-07-14 Simplify
2025-07-14 Factor out more configuration.
2025-07-16 More SVD washing.
2025-07-16 Lazy wake-up on lpblink.
2025-07-17 Reduce BSS size.
2025-07-17 Get the 32 bit display working.
2025-07-18 Tweaks to PUPD handling, and no-debug.
2025-07-19 Fewer ways to hang on panics etc.
2025-07-19 Simplify.
2025-07-19 const derive!
2025-07-19 Rename!
2025-07-20 Split out a python module
2025-07-20 Little tidies.
2025-07-21 Update notes on schematic.
2025-07-21 Little tidy ups.
2025-07-21 Tidy-up the rtc handling.
2025-07-21 Start beaking out clocky.
2025-07-21 Rename
2025-07-23 Main display modes.
2025-07-24 More split out.
    Reduce binary size by avoiding format!s.
2025-07-26 Feature complete :-)
2025-07-26 Work flow simplification.
2025-07-26 Little clean-ups.
2025-07-27 Implement cal mode.
    Improve workflow.
2025-07-27 Oscillator output.
    Simplify.
2025-07-27 Bug fix.
2025-07-29 Enhance adjustments for 4 digit display.
2025-07-29 Looks like we need a little more crystal drive.
2025-07-31 Split monitor for the two revs.
    Put in support for the new rev & second vsense channel.
2025-07-31 Tidy and bug fix.
2025-08-01 Tweak ADC start-up.
2025-08-01 Manky calibration code. Manky accel handling.
2025-08-01 Don't need static_assertions.
2025-08-02 Get accel hooked in sensibly & implement screen flip.
2025-08-02 Tidy up. Get rid of format from the small build.
2025-08-03 Update resistor values.
2025-08-03 Make temp the default display; it's useful on an unconfigured device.
2025-08-03 Detect touch threshold at run time.
    Redo touch evaluation.
2025-08-14 Add clock drive and crash address.
2025-08-14 Retire some old code.
2025-08-16 Simplify and fix and temperature handling.
2025-08-16 Correct handling of weekday.
2025-08-29 Fix no-debug.
    Update offset.
2025-10-26 Update schematic with pressure and humidity.
2025-10-27 Update PCB layout. Song and dance with Kicad breaking footprints...
2025-10-28 Manufacturing updates.
2025-11-27 Use latest compiler.
2025-11-27 Put in states for pressure / humidity.
    Wrappers & free up some RTC state space.
2025-11-27 Sync up I2C.
2025-11-27 Rationalise TSC handling a bit.
2025-11-27 Demo ENS code
2025-11-27 Add a random voltage regulator.
2025-11-27 Retire the blinky.
2025-11-28 Sanish humidity handling
2025-11-28 Fix the double wait!
2025-11-28 Pressure handling
2025-11-28 We exceed 16 bits on the decimal conversion now...
2025-11-29 Pressure position.
    Various refactoring. And blink when ext-osc is on.
2025-11-29 Split up some source files
2025-11-29 Put the ENS212 into low power mode.
    Minor tweaks.
2025-11-30 Make a config state out of touch evaluation.
2025-11-30 Fix a silly typo.
    Rename 'scract' to 'touch_debug'
2025-11-30 I can't read.
2025-12-01 Update board with 1.8V power domain.
2025-12-03 Tweak a component.
2025-12-03 Typecheck filter_pos.py
2025-12-03 Refactoring around numeric formatting.
2025-12-03 Convert the PAC to a submodule
2025-12-04 I2C and debug go to common code
2025-12-04 We only need one I2C context...
    Get rid of some wildard uses.
2025-12-06 Move some shared code to a proper crate.
2025-12-06 Debug is shared.
2025-12-06 Sync with latest API changes.
2025-12-06 Cratify I2C.
2025-12-07 Track I2C.
2025-12-07 Tweaks & simplify.
2025-12-07 Remove submodule
2025-12-07 Update to latest konst.
2025-12-07 Reify the debug meta-data.
2025-12-07 Rationalisation.
2025-12-15 Fix the pressure DP with 6 digits.
2026-06-29 Trim unused features.
